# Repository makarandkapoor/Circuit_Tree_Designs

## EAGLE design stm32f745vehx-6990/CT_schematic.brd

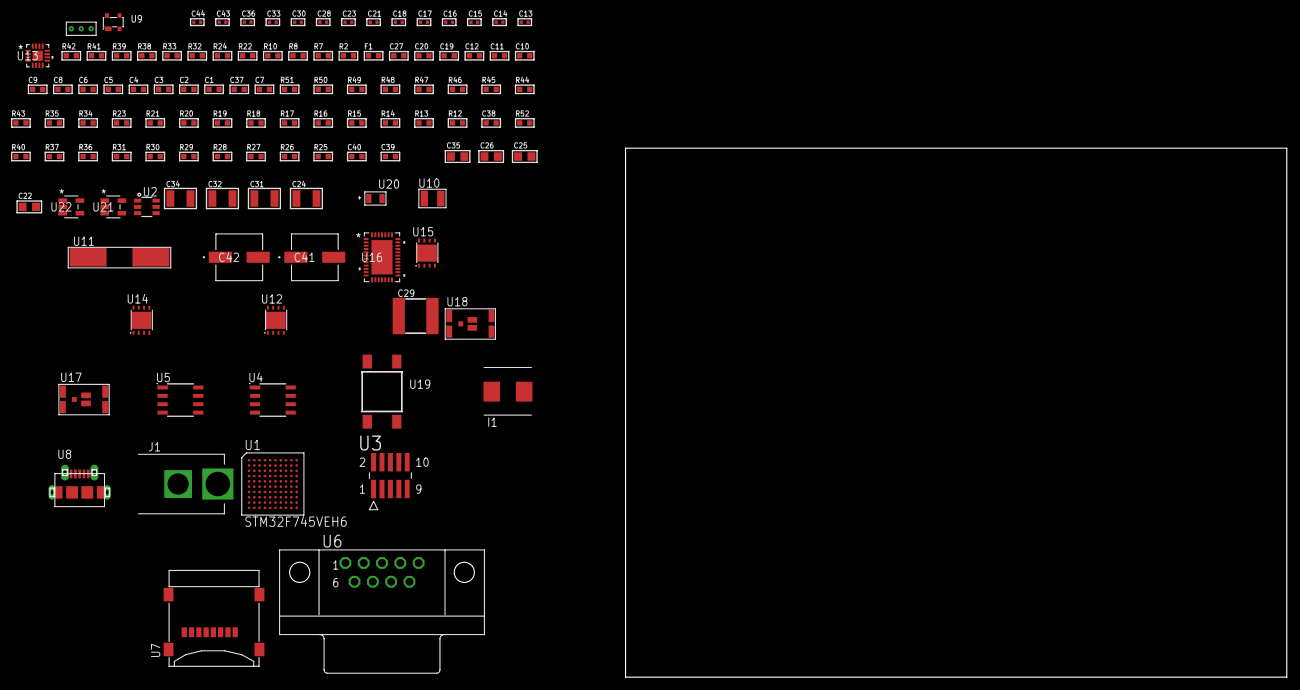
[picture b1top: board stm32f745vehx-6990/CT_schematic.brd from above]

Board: 2 copper layers, 115 parts (0 on the bottom side), 78 nets, no tracks yet.

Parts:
C1, C9, C19, C20, C27: 1e-06; C0603
C2, C3, C4, C5, C6, C10, C11, C12: 1e-07; C0603
C7: 4.7e-06; C0603
C8: 1e-08; C0603
C13, C14, C15, C16: 1e-11; C0402
C17, C21, C28, C36: 1e-07; C0402
C18, C23, C30, C33, C43, C44: 1e-08; C0402
C22, C25, C26, C35: 1e-05; C0805
C24, C31, C32, C34: 1e-05; C1210
C29: 6.8e-05; 2220
C37: 2.2e-06; C0603
C38: 2.45e-08; R0603
C39: 2.8258362168397e-09; R0603
C40: 7.105e-09; R0603
C41, C42: 0.0001; EXV-9H
F1: 240.0; L0603
I1: 3.3e-06; WE-HCI_7030/7040/7050
J1: PJ-037B; PJ-037B_PACKAGE
R2, R33, R39, R42: 1000.0; R0603
R7: 4700.0; R0603
R8, R10: 2200.0; R0603
R12: 47000.0; R0603
R13, R14, R15, R16, R17, R18, R19, R20, R21, R23, R43, R45, R46, R49, R50, R51: 10000.0; R0603
R22: 5.0; R0603
R24: 120.0; R0603
R25, R26, R27, R28, R29, R30, R31, R37, R40, R52: 100000.0; R0603
R32, R41: 200.0; R0603
R34: 20000.0; R0603
R35: 39000.0; R0603
R36: 300000.0; R0603
R38: 3900.0; R0603
R44: 75000.0; R0603
R47, R48: 95300.0; R0603
U1: STM32F745VEH6; TFBGA100
U2: MAX4995AAUT+T; SOT-23-6
U3: FTSH-105-01-L-DV-K; SAMTEC_FTSH-105-01-L-DV-K
U4: M24M02-DRMN6TP; SOIC-8
U5: MCP2562-E/SN; SOIC-8
U6: 182-009-113R531; 182-009-MALE
U7: 0472192001; MOLEX_47219-2001
U8: 47590-0001; MICRO_USB_AB
U9: prtr5v0u2ax; SOT143B
U10: ABS07-32.768KHZ-7-T
U11: ABLS-25.000MHZ-B2F-T
U12, U14, U15: LP3878SDX-ADJ/NOPB; WSON-8
U13: LTC3601EUD#PBF; QFN-16_EP
U16: LTC2928CUHF#PBF; QFN-38_UHF
U17, U18: IRF8306MTRPbF; IRF8306MTRPBF
U19: 4-1437565-2; SW_4-1437565-2
U20: Q65110A2395; LGM67K-G1J2-24-Z
U21, U22: nc7sz125m5x; NC7SZ125M5X
U23: Dummy; DUMMY_PACKAGE_257

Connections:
CLK_CRYSTAL_U1_A1: C13.1, U1.A1, U10.1
CLK_CRYSTAL_U1_B1: C14.1, U1.B1, U10.2
CLK_CRYSTAL_U1_C1: C15.1, U1.C1, U11.1
CLK_CRYSTAL_U1_D1: C16.1, U1.D1, U11.2
GND: C1.2, C2.2, C3.2, C4.2, C5.2, C6.2, C7.2, C8.2, C9.2, C10.2, C11.2, C12.2, C13.2, C14.2, C15.2, C16.2, C17.2, C18.2, C19.2, C20.2, C21.2, C22.2, C23.2, C24.2, C25.2, C26.2, C27.2, C29.1, C29.2, C30.2, C31.2, C32.2, C33.2, C34.2, C35.2, C36.2, C37.2, C38.2, C39.2, C40.2, C41.2, C42.2, C43.2, C44.2, J1.2, R2.2, R12.2, R13.2, R17.2, R21.2, R22.2, R23.2, R33.2, R34.2, R36.2, R39.2, R42.2, R44.2, R47.2, R48.2, R49.2, R50.2, R51.2, U1.C2, U1.E4, U1.E5, U1.G1, U1.J1, U2.2, U3.3, U3.5, U4.4, U5.2, U5.8, U6.5, U7.6, U7.G1, U7.G2, U7.G3, U7.G4, U8.5, U8.6, U8.7, U8.8, U8.9, U9.1, U12.3, U12.PAD, U13.1, U13.9, U13.17, U14.3, U14.PAD, U15.3, U15.PAD, U16.8, U16.9, U16.10, U16.12, U16.13, U16.24, U16.25, U16.30, U16.32, U16.39, U20.C, U21.2, U21.3, U22.1, U22.3, U23.1
NET_U1_A5: R10.1, U1.A5, U4.5
NET_U1_B4: R8.1, U1.B4, U4.6
NET_U1_D5: R13.1, U1.D5
NET_U1_E1: R7.1, U1.E1, U22.4
NET_U1_E6: R15.1, U1.E6
NET_U1_E7: C12.1, U1.E7
NET_U1_F7: R14.1, U1.F7
NET_U1_H1: C8.1, C9.1, F1.1, U1.H1
NET_U1_K10: U19.3, U19.4
NET_U2_3: R12.1, U2.3
NET_U3_9: R22.1, U3.9
NET_U4_3: R23.1, U4.3
NET_U5_6: R24.2, U5.6
NET_U6_2: R24.2, U5.6, U6.2
NET_U6_3: R24.1, U5.7, U6.3
NET_U12_1: C23.1, U12.1
NET_U12_6: R32.2, R33.1, U12.6
NET_U12_8: R31.1, U12.8
NET_U13_3: C28.2, I1.1, U13.3, U13.4
NET_U13_6: C28.1, U13.6
NET_U13_7: C27.1, U13.7, U13.12
NET_U13_10: R36.1, U13.10
NET_U13_11: R34.1, R35.1, U13.11
NET_U13_ATNET_3: I1.2, R35.2
NET_U14_1: C30.1, U14.1
NET_U14_6: R38.2, R39.1, U14.6
NET_U14_8: R37.1, U14.8
NET_U15_1: C33.1, U15.1
NET_U15_6: R41.2, R42.1, U15.6
NET_U15_8: R40.1, U15.8
NET_U16_3: R50.1, U16.3
NET_U16_6: R47.1, U16.6
NET_U16_7: R48.1, U16.7
NET_U16_16: R49.1, R52.1, U16.16
NET_U16_18: R46.1, U16.18
NET_U16_19: R45.1, U16.19, U16.20
NET_U16_21: R43.1, R44.1, U16.21, U21.4, U22.2
NET_U16_22: C36.1, R43.2, R45.2, R46.2, U16.11, U16.22
NET_U16_26: C39.1, U16.26
NET_U16_27: C38.1, U16.27
NET_U16_28: C40.1, U16.28
NET_U16_38: R51.1, U16.38
NET_U17_3: U16.2, U17.3
NET_U18_3: U16.37, U18.3
NET_U19_1: R2.1, U19.1, U19.2
PROC_CAN1_RX: U1.D8, U5.4
PROC_CAN1_TX: U1.A4, U5.1
PROC_GPIO_TO_U1_USB_FAULT: R16.1, U1.A3, U2.6
PROC_GPIO_TO_U1_VBUS_EN: R17.1, U1.A2, U2.4
PROC_SDMMC1_CK: R26.1, U1.C8, U7.5
PROC_SDMMC1_CMD: R25.1, U1.B7, U7.3
PROC_SDMMC1_D0: R27.1, U1.F9, U7.7
PROC_SDMMC1_D1: R28.1, U1.E9, U7.8
PROC_SDMMC1_D2: R29.1, U1.B9, U7.1
PROC_SDMMC1_D3: R30.1, U1.B8, U7.2
PROC_SYS_JTCK_SWCLK: R21.1, U1.A9, U3.4
PROC_SYS_JTDI: R19.1, U1.A8, U3.8
PROC_SYS_JTDO_SWO: U1.A7, U3.6
PROC_SYS_JTMS_SWDIO: R20.1, U1.A10, U3.2
PROC_TIM1_CH1: U1.D9, U23.2
PROC_TIM1_CH2N: U1.G6, U23.3
PROC_USB_OTG_FS_DM: U1.C10, U8.2, U9.3
PROC_USB_OTG_FS_DP: U1.B10, U8.3, U9.2
PROC_USB_OTG_FS_ID: U1.D10, U8.4
PROC_USB_OTG_FS_VBUS: U1.C9, U2.1, U8.1, U9.4
RST_OUT_U3_JTAG_RST_B: R18.1, U3.10, U21.1
VCC_12V0: C37.1, C41.1, C42.1, J1.1, R52.2, U16.23, U17.1, U17.2, U17.6, U17.7, U18.1, U18.2, U18.6, U18.7
VCC_S1_12V0: C24.1, C26.1, C31.1, R31.2, R37.2, U12.4, U13.15, U13.16, U14.4, U17.4, U17.5
VCC_S2_12V0: C34.1, R40.2, U15.4, U18.4, U18.5
VCC_TIER1_1V2: C11.1, C25.1, R32.1, U1.F8, U12.5
VCC_TIER1_1V8: C1.1, C2.1, C3.1, C4.1, C5.1, C6.1, C7.1, C10.1, C17.1, C18.1, C20.1, C21.1, C22.1, C29.2, C43.1, C44.1, F1.2, I1.2, R7.2, R8.2, R10.2, R14.2, R15.2, R16.2, R18.2, R19.2, R20.2, R25.2, R26.2, R27.2, R28.2, R29.2, R30.2, R35.2, U1.B2, U1.D2, U1.F4, U1.F5, U1.F6, U1.K1, U3.1, U4.8, U5.5, U7.4, U13.8, U21.5, U22.5
VCC_TIER1_5V0: C19.1, C32.1, R38.1, U2.5, U5.3, U14.5
VCC_TIER2_1V2: C35.1, R41.1, U15.5

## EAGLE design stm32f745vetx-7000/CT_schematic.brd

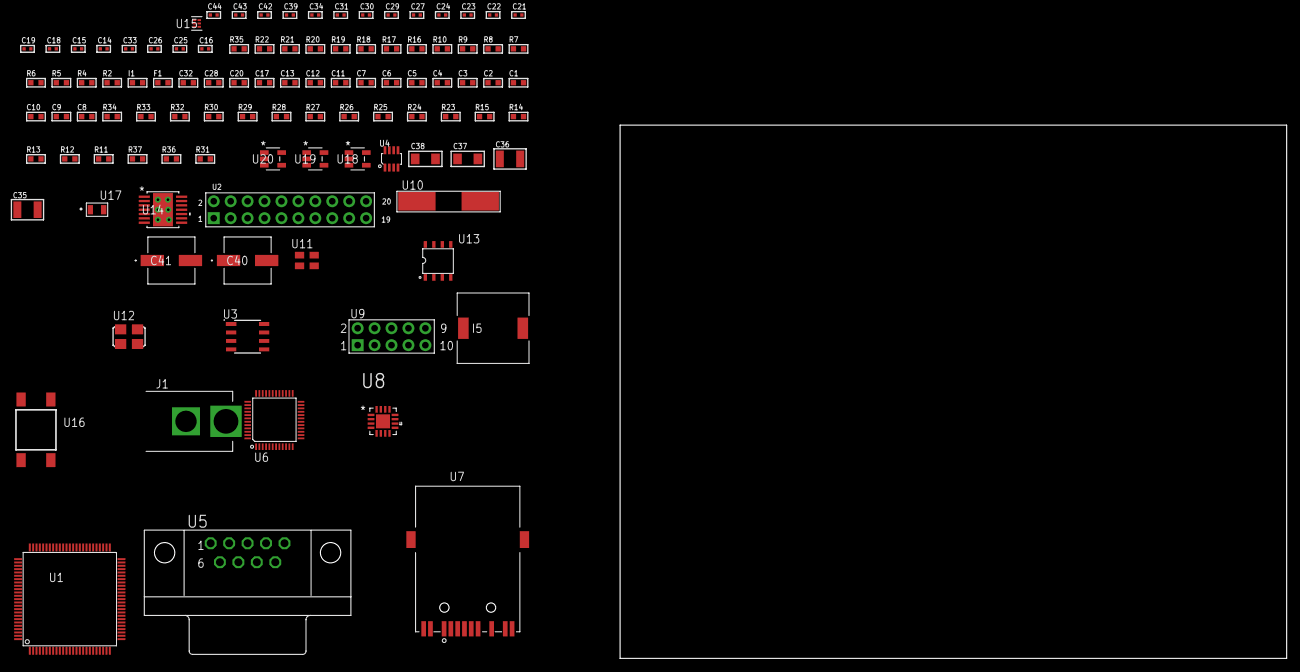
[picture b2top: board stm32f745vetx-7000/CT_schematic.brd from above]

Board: 2 copper layers, 100.0 x 80.0 mm, 103 parts (0 on the bottom side), 90 nets, no tracks yet.

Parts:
C1, C12, C13, C17, C20, C28, C32: 1e-06; C0603
C2, C3, C4, C5, C6, C7: 1e-07; C0603
C8: 4.7e-06; C0603
C9, C10: 2.2e-06; C0603
C11: 1e-08; C0603
C14, C19, C22, C29, C30, C31, C42, C43, C44: 1e-08; C0402
C15, C18, C21, C23, C24, C27, C34, C39: 1e-07; C0402
C16: 2.2e-08; C0402
C25, C26: 2.7e-11; C0402
C33: 3.3e-09; C0402
C35, C36: 2.2e-05; C1210
C37, C38: 1e-05; C1206
C40, C41: 0.0001; EXV-9H
F1: 240.0; L0603
I1: 97.0; R0603
I5: 5.2e-06; DR1040
J1: PJ-037B; PJ-037B_PACKAGE
R2: 1000.0; R0603
R4, R5, R6, R22: 4700.0; R0603
R7, R8, R9, R10: 2200.0; R0603
R11, R12, R13, R14, R15, R23, R24, R25, R26, R27, R28, R29, R30, R33, R34: 10000.0; R0603
R16: 120.0; R0603
R17, R18: 0.1; R0603
R19, R20: 200.0; R0603
R21: 2490.0; R0603
R31: 71007.101651032; R0603
R32: 22000.0; R0603
R35: 9100.0; R0603
R36: 680000.0; R0603
R37: 120000.0; R0603
U1: STM32F745VET6; LQFP100
U2: arducam_ov2640; ARDUCAM
U3: AT24C02D-SSHM-T; AT24C02D
U4: MAX3051EKA+T; SOT-23-8
U5: 182-009-113R531; 182-009-MALE
U6: RTL8201FL-VB-CG
U7: 7498011122R
U8: TSC2008TRGVRQ1; QFN65P400X400X100-17N
U9: HTSS-105-01-G-D
U10: ABLS-25.000MHZ-B2F-T
U11: ASEK-32.768KHz-ECST; ASEK
U12: ASFL1-25MHZ-NCS; ASFL1
U13: idt74fct38072; IDT74FCT38072
U14: tps54325PWP; HTSSOP14
U15: TPS3895ADRYR; SON-6
U16: 4-1437565-2; SW_4-1437565-2
U17: Q65110A2395; LGM67K-G1J2-24-Z
U18, U19, U20: nc7sz125m5x; NC7SZ125M5X

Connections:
CLK_CRYSTAL_U6_42: C26.1, U6.42, U10.1
CLK_CRYSTAL_U6_43: C25.1, U6.43, U10.2
CLK_U1_8: U1.8, U11.3
CLK_U1_12: U1.12, U13.6
CLK_U2_8: U2.8, U13.7
CLK_U13_3: U12.3, U13.3
GND: C1.2, C2.2, C3.2, C4.2, C5.2, C6.2, C7.2, C8.2, C9.2, C10.2, C11.2, C12.2, C13.2, C14.2, C15.2, C16.2, C17.2, C18.2, C19.2, C20.2, C21.2, C22.2, C23.2, C24.2, C25.2, C26.2, C27.2, C28.2, C29.2, C30.2, C31.2, C32.2, C33.2, C35.2, C36.2, C37.2, C38.2, C39.2, C40.2, C41.2, C42.2, C43.2, C44.2, J1.2, R2.2, R11.2, R12.2, R14.2, R15.2, R17.2, R18.2, R21.2, R23.2, R24.2, R26.2, R32.2, R35.2, R37.2, U1.10, U1.19, U1.26, U1.49, U1.74, U1.99, U2.2, U2.20, U3.4, U4.2, U4.8, U5.5, U6.7, U6.20, U6.33, U6.47, U7.9, U8.10, U8.12, U8.17, U9.9, U11.2, U12.2, U13.4, U13.5, U13.8, U14.5, U14.8, U14.9, U14.15, U15.2, U17.C, U18.1, U18.3, U19.1, U19.3, U20.1, U20.3
NET_U1_14: R5.1, U1.14, U19.4
NET_U1_16: R9.1, U1.16, U6.30
NET_U1_21: C11.1, C12.1, F1.1, U1.20, U1.21
NET_U1_24: R10.1, U1.24, U6.31
NET_U1_48: C9.1, U1.48
NET_U1_73: C10.1, U1.73
NET_U1_92: R7.1, U1.92, U3.6
NET_U1_94: R11.1, U1.94
NET_U1_96: R8.1, U1.96, U3.5
NET_U1_98: U16.3, U16.4
NET_U2_19: R6.1, U2.19, U20.4
NET_U3_1: R13.1, U3.1
NET_U3_2: R14.1, U3.2
NET_U3_3: R15.1, U3.3
NET_U3_7: R12.1, U3.7
NET_U4_6: R16.2, U4.6
NET_U5_2: R16.2, U4.6, U5.2
NET_U5_3: R16.1, U4.7, U5.3
NET_U6_6: C17.1, C18.1, C19.1, I1.1, U6.6, U6.41
NET_U6_10: R26.1, U6.10
NET_U6_29: R4.1, U6.29, U18.4
NET_U6_32: R22.1, U6.32
NET_U6_34: R24.1, U6.34
NET_U6_35: R25.1, U6.35
NET_U6_40: C24.1, U6.40
NET_U6_46: R21.1, U6.46
NET_U6_48: C23.1, U6.48
NET_U7_1: U6.1, U7.1
NET_U7_3: U6.2, U7.3
NET_U7_4: U6.4, U7.4
NET_U7_5: C16.1, U7.2, U7.5
NET_U7_6: U6.5, U7.6
NET_U7_8: R18.1, U7.8
NET_U7_10: R19.1, U7.10
NET_U7_12: R20.1, U7.12
NET_U7_13: R17.1, U7.13, U7.14
NET_U8_15: R30.1, U8.15
NET_U9_3: U8.7, U9.3
NET_U9_4: U8.9, U9.4
NET_U9_5: U8.6, U9.5
NET_U9_6: U8.8, U9.6
NET_U14_2: R31.2, R32.1, U14.2
NET_U14_3: C32.1, U14.3
NET_U14_4: C33.1, U14.4
NET_U14_10: C34.1, I5.1, U14.10, U14.11
NET_U14_12: C34.2, U14.12
NET_U15_1: R34.1, R35.1, U15.1
NET_U15_3: R36.2, R37.1, U15.3
NET_U15_4: R33.1, U15.4, U18.2, U19.2, U20.2
NET_U16_1: R2.1, U16.1, U16.2
PROC_CAN1_RX: U1.70, U4.4
PROC_CAN1_TX: U1.71, U4.1
PROC_DCMI_D0: U1.63, U2.18
PROC_DCMI_D1: U1.64, U2.17
PROC_DCMI_D2: U1.65, U2.16
PROC_DCMI_D3: U1.66, U2.15
PROC_DCMI_D4: U1.3, U2.14
PROC_DCMI_D5: U1.84, U2.13
PROC_DCMI_D6: U1.4, U2.12
PROC_DCMI_D7: U1.5, U2.11
PROC_DCMI_D8: U1.78, U2.10
PROC_DCMI_D9: U1.80, U2.9
PROC_DCMI_HSYNC: U1.28, U2.6
PROC_DCMI_PIXCLK: U1.30, U2.7
PROC_DCMI_VSYNC: U1.93, U2.5
PROC_ETH_COL: U1.25, U6.38
PROC_ETH_CRS: U1.22, U6.36
PROC_ETH_RXD0: U1.32, U6.14
PROC_ETH_RXD1: U1.33, U6.16
PROC_ETH_RXD2: U1.34, U6.17
PROC_ETH_RXD3: R27.1, U6.18
PROC_ETH_RX_CLK: U1.23, U6.19
PROC_ETH_RX_DV: R23.1, U1.31, U6.13
PROC_ETH_RX_ER: R28.1, U6.39
PROC_ETH_TXD2: U1.17, U6.25
PROC_ETH_TXD3: U1.1, U6.26
PROC_ETH_TX_CLK: U1.18, U6.22
PROC_SPI1_MISO: U1.90, U8.16
PROC_SPI1_MOSI: U1.91, U8.2
PROC_SPI1_NSS: R29.1, U1.77, U8.3
PROC_SPI1_SCK: U1.29, U8.4
VCC_S1_8V9: C37.1, C38.1, C40.1, C41.1, J1.1, U14.7, U14.13, U14.14
VCC_TIER1_3V3: C1.1, C2.1, C3.1, C4.1, C5.1, C6.1, C7.1, C8.1, C13.1, C14.1, C15.1, C20.1, C21.1, C22.1, C27.1, C28.1, C29.1, C30.1, C31.1, C35.1, C36.1, C39.1, C42.1, C43.1, C44.1, F1.2, I1.2, I5.2, R4.2, R5.2, R6.2, R7.2, R8.2, R9.2, R10.2, R13.2, R22.2, R25.2, R27.2, R28.2, R29.2, R30.2, R31.1, R33.2, R34.2, R36.1, U1.6, U1.11, U1.27, U1.50, U1.75, U1.100, U2.1, U3.8, U4.3, U6.15, U6.21, U6.37, U8.5, U11.4, U12.4, U13.1, U13.2, U14.1, U15.6, U18.5, U19.5, U20.5

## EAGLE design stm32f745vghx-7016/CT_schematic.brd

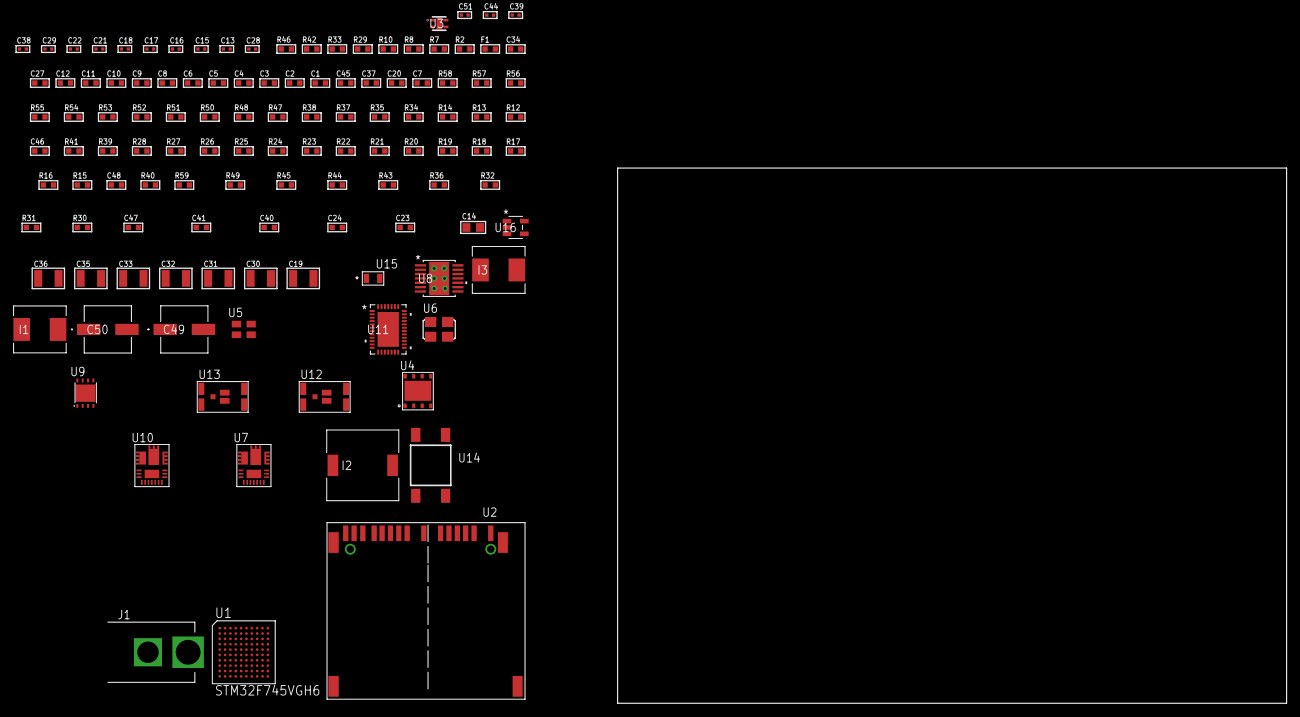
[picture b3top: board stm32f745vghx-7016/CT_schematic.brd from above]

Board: 2 copper layers, 100.0 x 80.0 mm, 120 parts (0 on the bottom side), 77 nets, no tracks yet.

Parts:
C1, C9, C27: 1e-06; C0603
C2, C3, C4, C5, C6, C10, C11, C12: 1e-07; C0603
C7: 4.7e-06; C0603
C8: 1e-08; C0603
C13, C15, C16, C21, C22, C29, C38, C39, C44: 1e-07; C0402
C14: 1e-05; C0805
C17, C18, C51: 1e-08; C0402
C19, C36: 0.0001; C1210
C20, C37, C45: 2.2e-06; C0603
C23, C40: 8.6453388913681e-09; R0603
C24, C41: 2.9472746220573e-07; R0603
C28: 3.3e-09; C0402
C30, C31: 2.2e-05; C1210
C32, C33, C35: 1e-05; C1210
C34: 8e-07; R0603
C46: 2.45e-08; R0603
C47: 2.8258362168397e-09; R0603
C48: 7.105e-09; R0603
C49, C50: 0.0001; EXV-9H
F1: 240.0; L0603
I1, I3: 6.8e-07; IND25X25CZ
I2: 7e-06; DR1040
J1: PJ-037B; PJ-037B_PACKAGE
R2: 1000.0; R0603
R7: 4700.0; R0603
R8, R10: 2200.0; R0603
R12, R13, R14, R50, R52, R53, R56, R57, R58: 10000.0; R0603
R15, R16, R17, R18, R19, R20, R21, R22, R23, R24, R25, R26, R27, R28, R39, R41: 100000.0; R0603
R29, R42: 0.1; R0603
R30, R43: 4030.2416170974; R0603
R31, R44: 2878.7440122125; R0603
R32, R45: 58.964311377246; R0603
R33, R46: 130.0; R0603
R34, R47: 39000.0; R0603
R35, R48: 49900.0; R0603
R36, R49: 5181.6688741722; R0603
R37: 30000.0; R0603
R38: 22000.0; R0603
R40: 153694.38; R0603
R51: 75000.0; R0603
R54, R55: 95300.0; R0603
R59: 138981.81818182; R0603
U1: STM32F745VGH6; TFBGA100
U2: 10100565
U3: Si7034-A10-IM; SI7034-A10-IM
U4: SST26WF016B-104I/MF; WFDN-8
U5: ASEK-32.768KHz-ECST; ASEK
U6: ASFL1-25MHZ-NCS; ASFL1
U7, U10: IR3899MTR1PBF
U8: tps54225PWP; HTSSOP14
U9: LP2951ACSDX/NOPB; WSON-8
U11: LTC2928CUHF#PBF; QFN-38_UHF
U12, U13: IRF8306MTRPbF; IRF8306MTRPBF
U14: 4-1437565-2; SW_4-1437565-2
U15: Q65110A2395; LGM67K-G1J2-24-Z
U16: nc7sz125m5x; NC7SZ125M5X

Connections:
CLK_U1_A1: U1.A1, U5.3
CLK_U1_C1: U1.C1, U6.3
GND: C1.2, C2.2, C3.2, C4.2, C5.2, C6.2, C7.2, C8.2, C9.2, C10.2, C11.2, C12.2, C13.2, C14.2, C15.2, C16.2, C17.2, C18.2, C20.2, C21.2, C22.2, C27.2, C28.2, C30.2, C31.2, C32.2, C33.2, C34.2, C35.2, C37.2, C38.2, C39.2, C44.2, C45.2, C46.2, C47.2, C48.2, C49.2, C50.2, C51.2, J1.2, R2.2, R12.2, R29.1, R29.2, R31.2, R34.2, R36.2, R38.2, R41.2, R42.1, R42.2, R44.2, R47.2, R49.2, R51.2, R54.2, R55.2, R56.2, R57.2, R58.2, U1.C2, U1.E4, U1.E5, U1.G1, U1.J1, U2.6, U2.10, U2.12, U2.16, U2.17, U2.20, U2.21, U3.5, U4.4, U4.9, U5.2, U6.2, U7.4, U7.11, U7.17, U8.5, U8.8, U8.9, U8.15, U9.3, U9.4, U9.PAD, U10.4, U10.11, U10.17, U11.8, U11.9, U11.10, U11.12, U11.13, U11.24, U11.25, U11.30, U11.32, U11.39, U15.C, U16.1, U16.3
NET_U1_D5: R12.1, U1.D5
NET_U1_E1: R7.1, U1.E1, U16.4
NET_U1_E6: R14.1, U1.E6
NET_U1_E7: C12.1, U1.E7
NET_U1_F7: R13.1, U1.F7
NET_U1_H1: C8.1, C9.1, F1.1, U1.H1
NET_U1_J7: R8.1, U1.J7, U3.2
NET_U1_K7: R10.1, U1.K7, U3.4
NET_U1_K9: U14.3, U14.4
NET_U2_1: R17.1, U2.1
NET_U2_2: R16.1, U2.2
NET_U2_18: U2.18, U2.19
NET_U7_1: C23.1, R30.1, R31.1, R32.1, R33.1, U7.1, U7.8
NET_U7_2: C22.1, U7.2
NET_U7_3: C23.2, C24.1, C24.2, U7.3
NET_U7_5: R34.1, U7.5
NET_U7_10: C20.1, U7.10
NET_U7_12: C19.1, I1.1, U7.12
NET_U7_14: C19.2, U7.14
NET_U7_15: R35.1, R36.1, U7.15
NET_U7_ATNET_3: I1.2, R30.2
NET_U7_ATNET_4: C24.2, R32.2
NET_U8_2: R37.2, R38.1, U8.2
NET_U8_3: C27.1, U8.3
NET_U8_4: C28.1, U8.4
NET_U8_10: C29.1, I2.1, U8.10, U8.11
NET_U8_12: C29.2, U8.12
NET_U9_5: R39.1, U9.5
NET_U9_7: R40.2, R41.1, U9.7
NET_U10_1: C40.1, R43.1, R44.1, R45.1, R46.1, U10.1, U10.8
NET_U10_2: C39.1, U10.2
NET_U10_3: C40.2, C41.1, C41.2, U10.3
NET_U10_5: R47.1, U10.5
NET_U10_10: C37.1, U10.10
NET_U10_12: C36.1, I3.1, U10.12
NET_U10_14: C36.2, U10.14
NET_U10_15: R48.1, R49.1, U10.15
NET_U10_ATNET_3: I3.2, R43.2
NET_U10_ATNET_4: C41.2, R45.2
NET_U11_3: R57.1, U11.3
NET_U11_6: R54.1, U11.6
NET_U11_7: R55.1, U11.7
NET_U11_16: R56.1, R59.1, U11.16
NET_U11_18: R53.1, U11.18
NET_U11_19: R52.1, U11.19, U11.20
NET_U11_21: R50.1, R51.1, U11.21, U16.2
NET_U11_26: C47.1, U11.26
NET_U11_27: C46.1, U11.27
NET_U11_28: C48.1, U11.28
NET_U11_38: R58.1, U11.38
NET_U12_3: U11.2, U12.3
NET_U13_3: U11.37, U13.3
NET_U14_1: R2.1, U14.1, U14.2
PROC_QUADSPI_BK1_IO0: U1.G9, U4.5
PROC_QUADSPI_BK1_IO1: U1.K10, U4.2
PROC_QUADSPI_BK1_IO2: R27.1, U1.A3, U4.3
PROC_QUADSPI_BK1_IO3: R28.1, U1.H2, U4.7
PROC_QUADSPI_BK1_NCS: R26.1, U1.B5, U4.1
PROC_QUADSPI_CLK: U1.G5, U4.6
PROC_SDMMC1_CK: R15.1, U1.C8, U2.8
PROC_SDMMC1_D0: R18.1, U1.F9, U2.4
PROC_SDMMC1_D1: R19.1, U1.E9, U2.3
PROC_SDMMC1_D2: R20.1, U1.B9, U2.15
PROC_SDMMC1_D3: R21.1, U1.B8, U2.14
PROC_SDMMC1_D4: R22.1, U1.B4, U2.13
PROC_SDMMC1_D5: R23.1, U1.A4, U2.11
PROC_SDMMC1_D6: R24.1, U1.F10, U2.7
PROC_SDMMC1_D7: R25.1, U1.E10, U2.5
VCC_16V7: C44.1, C45.1, C49.1, C50.1, J1.1, R50.2, R52.2, R53.2, R59.2, U11.11, U11.22, U12.1, U12.2, U12.6, U12.7, U13.1, U13.2, U13.6, U13.7
VCC_S1_16V7: C21.1, C32.1, C33.1, C34.1, R35.2, U7.9, U8.7, U8.13, U8.14, U9.8, U12.4, U12.5
VCC_S2_16V7: C38.1, R48.2, U10.9, U13.4, U13.5
VCC_TIER1_1V2: C11.1, I1.2, R30.2, U1.F8
VCC_TIER1_1V8: C1.1, C2.1, C3.1, C4.1, C5.1, C6.1, C7.1, C13.1, C14.1, C15.1, C16.1, C30.1, C31.1, C51.1, F1.2, I2.2, R7.2, R8.2, R10.2, R13.2, R14.2, R15.2, R16.2, R17.2, R18.2, R19.2, R20.2, R21.2, R22.2, R23.2, R24.2, R25.2, R26.2, R27.2, R28.2, R37.1, U1.B2, U1.D2, U1.F4, U1.F5, U1.K1, U2.9, U3.1, U4.8, U8.1, U16.5
VCC_TIER1_3V3: C10.1, C17.1, C18.1, C35.1, R39.2, R40.1, U1.F6, U5.4, U6.4, U9.1
VCC_TIER2_1V2: I3.2, R43.2

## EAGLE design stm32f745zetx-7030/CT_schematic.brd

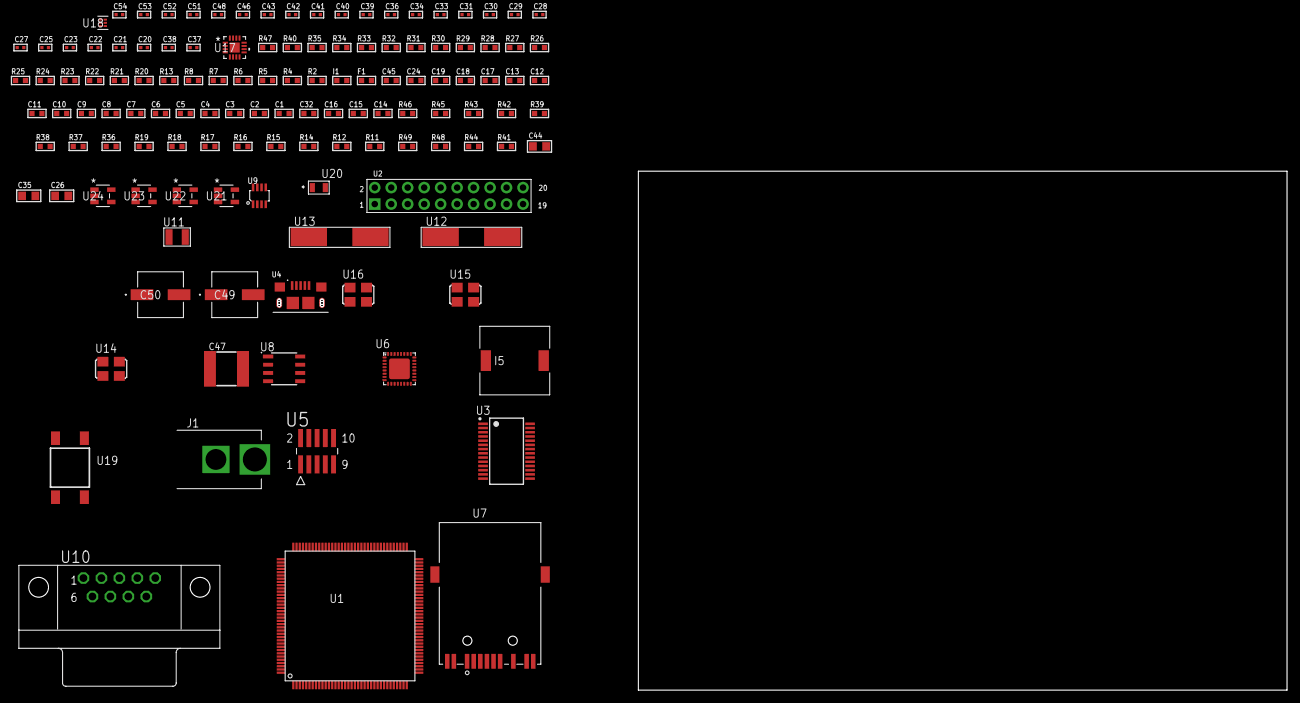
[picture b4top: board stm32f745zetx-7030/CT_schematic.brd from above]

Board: 2 copper layers, 127 parts (0 on the bottom side), 95 nets, no tracks yet.

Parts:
C1, C18, C24, C45: 1e-06; C0603
C2, C3, C4, C5, C6, C7, C8, C9, C10, C11, C12, C13, C19: 1e-07; C0603
C14: 4.7e-06; C0603
C15, C16, C32: 2.2e-06; C0603
C17: 1e-08; C0603
C20, C21, C22, C23: 1e-11; C0402
C25, C27, C28, C29, C30, C31, C33, C34, C36, C40, C46, C48: 1e-07; C0402
C26: 4.7e-06; C0805
C35, C44: 1e-05; C0805
C37, C38: 2.2e-11; C0402
C39, C41, C42, C43, C51, C52, C53, C54: 1e-08; C0402
C47: 6.8e-05; 2220
C49, C50: 0.0001; EXV-9H
F1: 240.0; L0603
I1: 97.0; R0603
I5: 3.8e-06; DR1040
J1: PJ-037B; PJ-037B_PACKAGE
R2, R30, R32: 1000.0; R0603
R4, R5, R6, R13, R26, R27, R28, R29, R31, R33, R34, R35: 4700.0; R0603
R7, R8: 2200.0; R0603
R11, R12, R14, R15, R16, R17, R18, R19, R36, R37, R38, R39, R45, R46: 10000.0; R0603
R20: 5.0; R0603
R21, R22: 0.1; R0603
R23: 200.0; R0603
R24: 220.0; R0603
R25: 6490.0; R0603
R40: 120.0; R0603
R41: 100000.0; R0603
R42: 20000.0; R0603
R43: 91000.0; R0603
R44: 300000.0; R0603
R47: 9100.0; R0603
R48: 680000.0; R0603
R49: 120000.0; R0603
U1: STM32F745ZET6; LQFP144
U2: arducam_ov2640; ARDUCAM
U3: FT232RL-REEL; SSOP-28
U4: 10118193-0001LF; FCI_10118193-0001LF
U5: FTSH-105-01-L-DV-K; SAMTEC_FTSH-105-01-L-DV-K
U6: KSZ8081RNBIA-TR; QFN-32
U7: 7498011122R
U8: AT24C02D-SSHM-T; AT24C02D
U9: MAX3051EKA+T; SOT-23-8
U10: 182-009-113R531; 182-009-MALE
U11: ABS07-32.768KHZ-7-T
U12, U13: ABLS-25.000MHZ-B2F-T
U14: ASFL1-12MHZ-NCS; ASFL1
U15: ASFL1-25MHZ-NCS; ASFL1
U16: ASFL1-50MHZ-NCS; ASFL1
U17: LTC3601EUD#PBF; QFN-16_EP
U18: TPS3895ADRYR; SON-6
U19: 4-1437565-2; SW_4-1437565-2
U20: Q65110A2395; LGM67K-G1J2-24-Z
U21, U22, U23, U24: nc7sz125m5x; NC7SZ125M5X

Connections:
CLK_CRYSTAL_U1_8: C20.1, U1.8, U11.1
CLK_CRYSTAL_U1_9: C21.1, U1.9, U11.2
CLK_CRYSTAL_U1_23: C22.1, U1.23, U12.1
CLK_CRYSTAL_U1_24: C23.1, U1.24, U12.2
CLK_CRYSTAL_U6_8: C37.1, U6.8, U13.2
CLK_CRYSTAL_U6_9: C38.1, U6.9, U13.1
CLK_U1_35: U1.35, U16.3
CLK_U2_8: U2.8, U15.3
CLK_U3_27: U3.27, U14.3
GND: C1.2, C2.2, C3.2, C4.2, C5.2, C6.2, C7.2, C8.2, C9.2, C10.2, C11.2, C12.2, C13.2, C14.2, C15.2, C16.2, C17.2, C18.2, C19.2, C20.2, C21.2, C22.2, C23.2, C24.2, C25.2, C26.2, C27.2, C28.2, C29.2, C30.2, C31.2, C32.2, C33.2, C34.2, C35.2, C36.2, C37.2, C38.2, C39.2, C40.2, C41.2, C42.2, C43.2, C44.2, C45.2, C47.1, C47.2, C48.2, C49.2, C50.2, C51.2, C52.2, C53.2, C54.2, J1.2, R2.2, R11.2, R15.2, R19.2, R20.2, R21.2, R22.2, R25.2, R27.2, R30.2, R32.2, R36.2, R38.2, R39.2, R41.2, R42.2, R44.2, R47.2, R49.2, U1.16, U1.31, U1.38, U1.51, U1.61, U1.83, U1.94, U1.107, U1.120, U1.130, U2.2, U2.20, U3.7, U3.18, U3.21, U3.25, U3.26, U4.5, U4.6, U4.7, U4.8, U4.9, U5.3, U5.5, U6.1, U6.EXP, U7.1, U7.10, U8.4, U9.2, U10.5, U14.2, U15.2, U16.2, U17.1, U17.9, U17.17, U18.2, U20.C, U21.2, U21.3, U22.1, U22.3, U23.1, U23.3, U24.1, U24.3
NET_U1_25: R5.1, U1.25, U23.4
NET_U1_33: C17.1, C18.1, F1.1, U1.32, U1.33
NET_U1_71: C15.1, U1.71
NET_U1_106: C16.1, U1.106
NET_U1_136: R7.1, U1.136, U8.6
NET_U1_137: R8.1, U1.137, U8.5
NET_U1_138: R11.1, U1.138
NET_U1_142: U19.3, U19.4
NET_U1_143: R12.1, U1.143
NET_U2_19: R6.1, U2.19, U24.4
NET_U3_14: R14.1, U3.14
NET_U3_17: C27.1, U3.17
NET_U3_19: R15.1, U3.19
NET_U4_1: R13.1, U4.1
NET_U4_2: U3.16, U4.2
NET_U4_3: U3.15, U4.3
NET_U5_9: R20.1, U5.9
NET_U6_2: C32.1, C33.1, U6.2
NET_U6_3: C34.1, I1.1, U6.3
NET_U6_10: R25.1, U6.10
NET_U6_13: R28.1, U6.13
NET_U6_14: R29.1, U6.14
NET_U6_19: R27.1, U6.19
NET_U6_20: R33.1, U6.20
NET_U6_21: R26.1, U6.21
NET_U6_28: R31.1, U6.28
NET_U6_29: R32.1, U6.29
NET_U6_31: R34.1, U6.31
NET_U6_32: R4.1, U6.32, U22.4
NET_U7_1: U6.7, U7.1
NET_U7_2: C30.1, U7.2
NET_U7_3: U6.6, U7.3
NET_U7_4: U6.5, U7.4
NET_U7_5: C31.1, U7.5
NET_U7_6: U6.4, U7.6
NET_U7_8: R22.1, U7.8
NET_U7_9: R23.1, U7.9
NET_U7_12: R24.1, U7.12
NET_U7_13: R21.1, U7.13, U7.14
NET_U8_1: R37.1, U8.1
NET_U8_2: R38.1, U8.2
NET_U8_3: R39.1, U8.3
NET_U8_7: R36.1, U8.7
NET_U9_6: R40.2, U9.6
NET_U9_8: R41.1, U9.8
NET_U10_2: R40.2, U9.6, U10.2
NET_U10_3: R40.1, U9.7, U10.3
NET_U17_3: C46.2, I5.1, U17.3, U17.4
NET_U17_6: C46.1, U17.6
NET_U17_7: C45.1, U17.7, U17.12
NET_U17_10: R44.1, U17.10
NET_U17_11: R42.1, R43.1, U17.11
NET_U17_ATNET_3: I5.2, R43.2
NET_U18_1: R46.1, R47.1, U18.1
NET_U18_3: R48.2, R49.1, U18.3
NET_U18_4: R45.1, U18.4, U21.4, U22.2, U23.2, U24.2
NET_U19_1: R2.1, U19.1, U19.2
PROC_CAN1_RX: U1.103, U9.4
PROC_CAN1_TX: U1.104, U9.1
PROC_DCMI_D0: U1.96, U2.18
PROC_DCMI_D1: U1.97, U2.17
PROC_DCMI_D2: U1.98, U2.16
PROC_DCMI_D3: U1.99, U2.15
PROC_DCMI_D4: U1.3, U2.14
PROC_DCMI_D5: U1.117, U2.13
PROC_DCMI_D6: U1.4, U2.12
PROC_DCMI_D7: U1.5, U2.11
PROC_DCMI_D8: U1.111, U2.10
PROC_DCMI_D9: U1.113, U2.9
PROC_DCMI_HSYNC: U1.40, U2.6
PROC_DCMI_PIXCLK: U1.42, U2.7
PROC_DCMI_VSYNC: U1.124, U2.5
PROC_ETH_RXD0: R35.1, U6.16
PROC_ETH_RXD1: R30.1, U6.15
PROC_SYS_JTCK_SWCLK: R19.1, U1.109, U5.4
PROC_SYS_JTDI: R17.1, U1.110, U5.8
PROC_SYS_JTDO_SWO: U1.133, U5.6
PROC_SYS_JTMS_SWDIO: R18.1, U1.105, U5.2
PROC_UART7_CTS: U1.21, U3.3
PROC_UART7_RTS: U1.20, U3.11
PROC_UART7_RX: U1.18, U3.1
PROC_UART7_TX: U1.19, U3.5
RST_OUT_U5_JTAG_RST_B: R16.1, U5.10, U21.1
VCC_S1_13V9: C44.1, C49.1, C50.1, J1.1, U17.15, U17.16
VCC_TIER1_3V3: C1.1, C2.1, C3.1, C4.1, C5.1, C6.1, C7.1, C8.1, C9.1, C10.1, C11.1, C12.1, C13.1, C14.1, C19.1, C24.1, C25.1, C26.1, C28.1, C29.1, C35.1, C36.1, C39.1, C40.1, C41.1, C42.1, C43.1, C47.2, C48.1, C51.1, C52.1, C53.1, C54.1, F1.2, I1.2, I5.2, R4.2, R5.2, R6.2, R7.2, R8.2, R12.2, R14.2, R16.2, R17.2, R18.2, R26.2, R28.2, R29.2, R31.2, R33.2, R34.2, R35.2, R37.2, R43.2, R45.2, R46.2, R48.1, U1.6, U1.17, U1.30, U1.39, U1.52, U1.62, U1.72, U1.84, U1.95, U1.108, U1.121, U1.131, U1.144, U2.1, U3.4, U3.20, U5.1, U6.17, U8.8, U9.3, U14.4, U15.4, U16.4, U17.8, U18.6, U21.5, U22.5, U23.5, U24.5

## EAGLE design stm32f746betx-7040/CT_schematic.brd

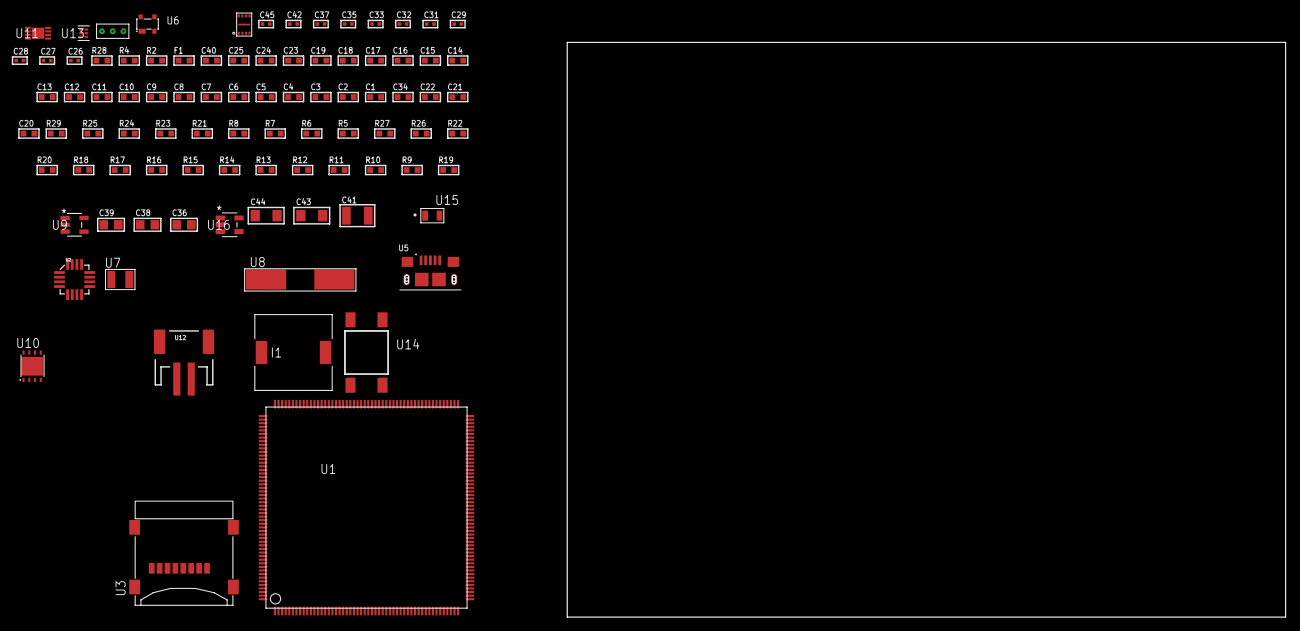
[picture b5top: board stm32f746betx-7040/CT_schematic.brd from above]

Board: 2 copper layers, 122.6 x 80.0 mm, 90 parts (0 on the bottom side), 48 nets, no tracks yet.

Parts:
C1, C24, C40: 1e-06; C0603
C2, C3, C4, C5, C6, C7, C8, C9, C10, C11, C12, C13, C14, C15, C16, C17, C18, C19, C25: 1e-07; C0603
C20: 4.7e-06; C0603
C21, C22: 2.2e-06; C0603
C23: 1e-08; C0603
C26, C27, C28, C29: 1e-11; C0402
C31, C32, C33, C45: 1e-08; C0402
C34: 4.7e-07; C0603
C35, C37, C42: 1e-07; C0402
C36, C38, C39: 1e-05; C0805
C41: 1e-05; C1210
C43, C44: 1e-05; C1206
F1: 240.0; L0603
I1: 3.8e-06; DR1040
R2: 1000.0; R0603
R4: 4700.0; R0603
R5, R6, R7, R8, R23, R24, R29: 10000.0; R0603
R9, R10, R11, R12, R13, R14, R15, R16, R17, R20, R22: 100000.0; R0603
R18: 490000.0; R0603
R19: 1000000.0; R0603
R21: 91000.0; R0603
R25: 82000.0; R0603
R26: 300000.0; R0603
R27: 120000.0; R0603
R28: 2000.0; R0603
U1: STM32F746BET6; LQFP208
U2: l3g4200d; LGA-16
U3: 0472192001; MOLEX_47219-2001
U4: SST26WF080BT-104I/NP; USON-8
U5: 10118193-0001LF; FCI_10118193-0001LF
U6: prtr5v0u2ax; SOT143B
U7: ABS07-32.768KHZ-7-T
U8: ABLS-25.000MHZ-B2F-T
U9: ltc3406es5; TSOT-23-5
U10: LP2951ACSDX/NOPB; WSON-8
U11: MCP73831T-2ACI/MC; DFN8_2X3MC
U12: S2B-PH-SM4-TB(LF)(SN); JST-2-SMD
U13: TPS3895ADRYR; SON-6
U14: 4-1437565-2; SW_4-1437565-2
U15: Q65110A2395; LGM67K-G1J2-24-Z
U16: nc7sz125m5x; NC7SZ125M5X
U17: Dummy; DUMMY_PACKAGE_194

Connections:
CLK_CRYSTAL_U1_9: C26.1, U1.9, U7.1
CLK_CRYSTAL_U1_10: C27.1, U1.10, U7.2
CLK_CRYSTAL_U1_32: C28.1, U1.32, U8.1
CLK_CRYSTAL_U1_33: C29.1, U1.33, U8.2
GND: C1.2, C2.2, C3.2, C4.2, C5.2, C6.2, C7.2, C8.2, C9.2, C10.2, C11.2, C12.2, C13.2, C14.2, C15.2, C16.2, C17.2, C18.2, C19.2, C20.2, C21.2, C22.2, C23.2, C24.2, C25.2, C26.2, C27.2, C28.2, C29.2, C31.2, C32.2, C33.2, C35.2, C36.2, C37.2, C38.2, C39.1, C39.2, C40.2, C41.2, C42.2, C43.2, C44.2, C45.2, R2.2, R5.2, R7.1, R7.2, R18.2, R22.2, R25.2, R27.2, R28.2, U1.14, U1.25, U1.40, U1.51, U1.60, U1.72, U1.82, U1.93, U1.114, U1.125, U1.136, U1.149, U1.170, U1.184, U1.202, U2.8, U2.9, U2.10, U2.11, U2.12, U2.13, U3.6, U3.G1, U3.G2, U3.G3, U3.G4, U4.4, U4.9, U5.5, U5.6, U5.7, U5.8, U5.9, U6.1, U9.2, U10.3, U10.4, U10.PAD, U11.6, U11.9, U12.2, U13.2, U15.C, U16.1, U16.3, U17.1
INPUT_USBPOWER_5V: C43.1, R29.2, U5.1, U6.4, U11.1, U11.2
NET_U1_34: R4.1, U1.34, U16.4
NET_U1_42: C23.1, C24.1, F1.1, U1.41, U1.42
NET_U1_92: C21.1, U1.92
NET_U1_148: C22.1, U1.148
NET_U1_197: R5.1, U1.197
NET_U1_203: R6.1, U1.203
NET_U1_208: U14.3, U14.4
NET_U2_14: C33.1, C34.1, U2.14
NET_U9_3: I1.1, U9.3
NET_U9_5: R18.1, R19.1, U9.5
NET_U9_ATNET_3: I1.2, R19.2
NET_U10_5: R20.1, U10.5
NET_U10_7: R21.2, R22.1, U10.7
NET_U11_5: R29.1, U11.5
NET_U11_8: R28.1, U11.8
NET_U13_1: R24.1, R25.1, U13.1
NET_U13_3: R26.2, R27.1, U13.3
NET_U13_4: R23.1, U13.4, U16.2
NET_U14_1: R2.1, U14.1, U14.2
PROC_PE3: U1.2, U17.2
PROC_PE4: U1.3, U17.3
PROC_QUADSPI_BK1_IO0: U1.29, U4.5
PROC_QUADSPI_BK1_IO1: U1.30, U4.2
PROC_QUADSPI_BK1_IO2: R16.1, U1.1, U4.3
PROC_QUADSPI_BK1_IO3: R17.1, U1.27, U4.7
PROC_QUADSPI_BK1_NCS: R15.1, U1.195, U4.1
PROC_QUADSPI_CLK: U1.63, U4.6
PROC_SDMMC1_CK: R10.1, U1.163, U3.5
PROC_SDMMC1_CMD: R9.1, U1.166, U3.3
PROC_SDMMC1_D0: R11.1, U1.140, U3.7
PROC_SDMMC1_D1: R12.1, U1.141, U3.8
PROC_SDMMC1_D2: R13.1, U1.161, U3.1
PROC_SDMMC1_D3: R14.1, U1.162, U3.2
PROC_SPI1_MISO: U1.55, U2.4
PROC_SPI1_MOSI: U1.56, U2.3
PROC_SPI1_NSS: R8.1, U1.53, U2.5
PROC_SPI1_SCK: U1.54, U2.2
PROC_USB_OTG_FS_DM: U5.2, U6.3
PROC_USB_OTG_FS_DP: U5.3, U6.2
VCC_S1_3V7: C38.1, C40.1, C44.1, U9.4, U10.8, U11.3, U11.4, U12.1
VCC_TIER1_1V8: C1.1, C2.1, C3.1, C4.1, C5.1, C6.1, C7.1, C8.1, C9.1, C10.1, C11.1, C12.1, C13.1, C14.1, C15.1, C16.1, C17.1, C18.1, C19.1, C20.1, C25.1, C32.1, C35.1, C36.1, C37.1, C39.2, C42.1, C45.1, F1.2, I1.2, R4.2, R6.2, R8.2, R9.2, R10.2, R11.2, R12.2, R13.2, R14.2, R15.2, R16.2, R17.2, R19.2, R23.2, R24.2, R26.1, U1.6, U1.15, U1.26, U1.39, U1.52, U1.59, U1.73, U1.83, U1.94, U1.103, U1.115, U1.124, U1.137, U1.150, U1.158, U1.171, U1.185, U1.204, U2.1, U3.4, U4.8, U13.6, U16.5
VCC_TIER1_2V5: C31.1, C41.1, R20.2, R21.1, U2.15, U2.16, U10.1
